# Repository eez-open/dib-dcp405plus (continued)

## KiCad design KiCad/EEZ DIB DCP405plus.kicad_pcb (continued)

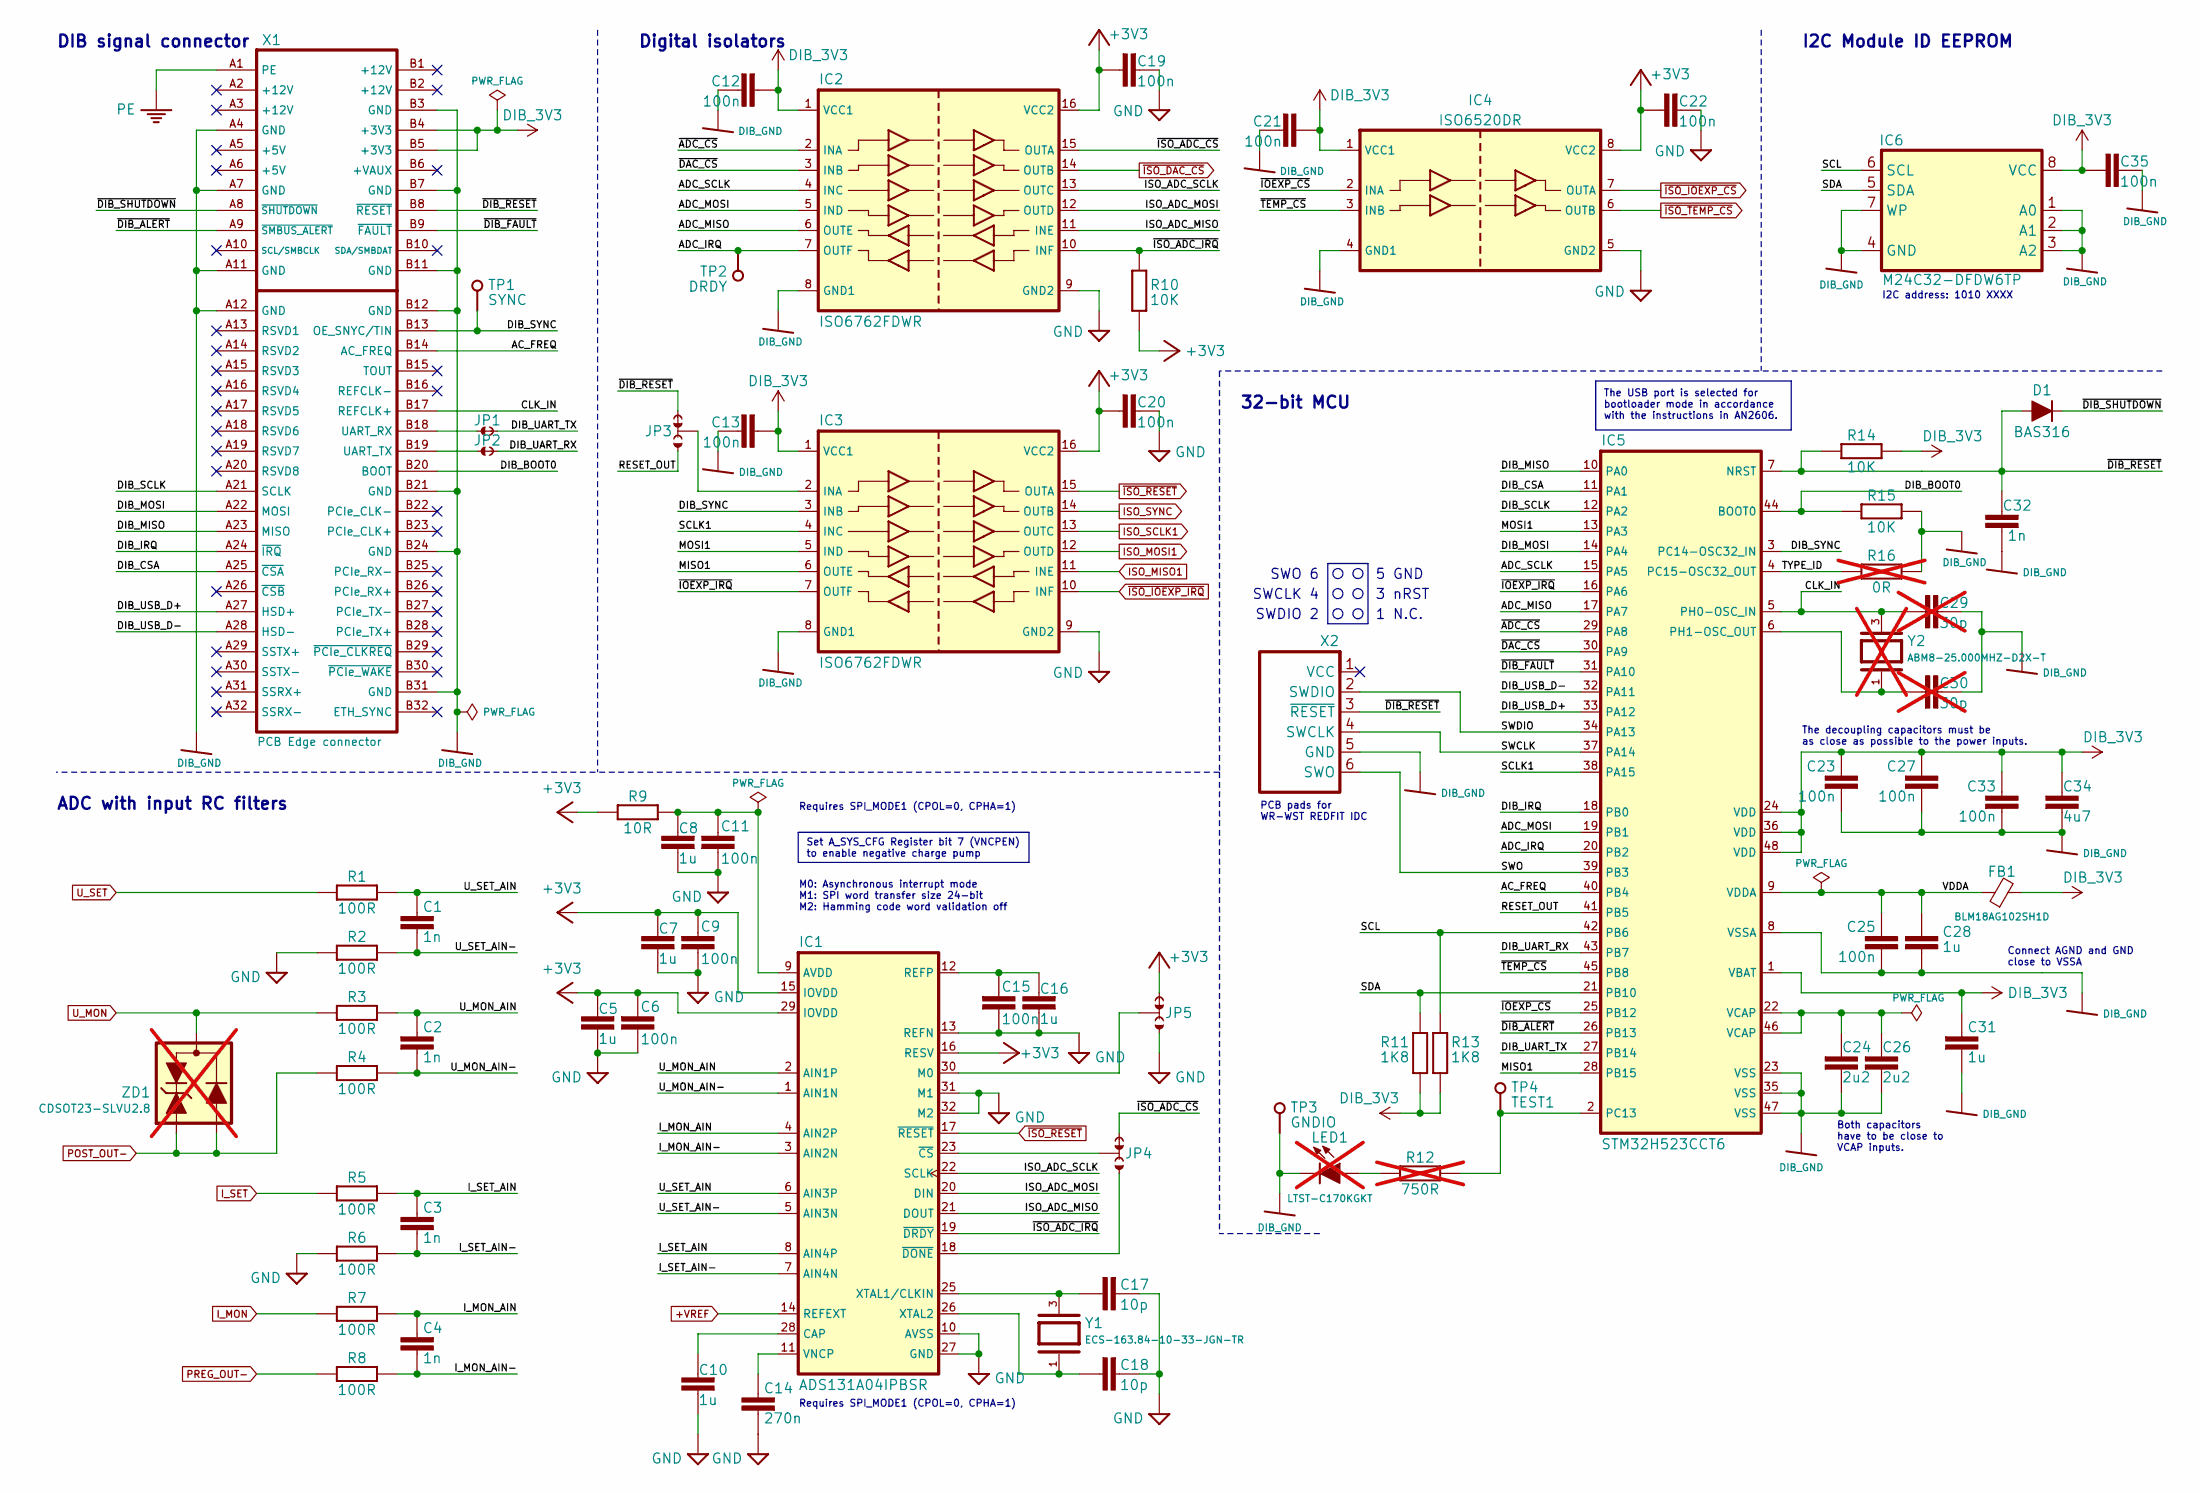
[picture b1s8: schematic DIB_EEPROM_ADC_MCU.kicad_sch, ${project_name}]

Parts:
C1, C2, C3, C4, C32: 1n; C_0603_1608Metric; DigiKey 1276-1018-1-ND
C5, C7, C8, C10, C16, C28, C31: 1u; C_0805_2012Metric; DigiKey 1276-2931-1-ND
C6, C9, C11, C12, C13, C15, C19, C20, C21, C22, C23, C25, C27, C33, C35: 100n; C_0603_1608Metric; DigiKey 1276-6717-1-ND
C14: 270n; C_0603_1608Metric; DigiKey 490-16405-1-ND
C17, C18: 10p; C_0603_1608Metric; DigiKey 1276-2149-1-ND
C24, C26: 2u2; C_0603_1608Metric; DigiKey 490-12332-1-ND
C29, C30: 30p; C_0603_1608Metric; DigiKey 1292-1515-1-ND; not fitted
C34: 4u7; C_0805_2012Metric; DigiKey 1276-2415-1-ND
D1: BAS316; SOD-323_1P8X1P35_ONS-M; DigiKey 5399-BAS316CT-ND
FB1: BLM18AG102SH1D; BEAD0603; DigiKey 490-7809-1-ND
IC1: ADS131A04IPBSR; QFP50P700X700X120-32N; DigiKey 296-44202-1-ND
IC2, IC3: ISO6762FDWR; DW16; DigiKey 296-ISO6762FDWRCT-ND
IC4: ISO6520DR; SOIC127P600X173-8N; DigiKey 296-ISO6520DRCT-ND
IC5: STM32H523CCT6; LQFP-48_7X7MM; DigiKey 497-STM32H523CCT6-ND
IC6: M24C32-DFDW6TP; TSSOP-8; DigiKey 497-16067-1-ND
JP1, JP2: JP2 shorted (0603)
JP3, JP4, JP5: 0R; JP3 shorted (0603)
LED1: LTST-C170KGKT; LED_LTST-C170KGKT_LTO-L; DigiKey 160-1414-2-ND; not fitted
R1, R2, R3, R4, R5, R6, R7, R8: 100R; R_0603_1608Metric; DigiKey 13-RC0603FR-10100RLCT-ND
R9: 10R; R_0805_2012Metric; DigiKey 311-10.0CRCT-ND
R10, R14, R15: 10K; R_0805_2012Metric; DigiKey 311-10.0KCRCT-ND
R11, R13: 1K8; R_0805_2012Metric; DigiKey 311-1.80KCRCT-ND
R12: 750R; R_0805_2012Metric; DigiKey A126385CT-ND; not fitted
R16: 0R; R_0603_1608Metric; not fitted
TP1, TP2, TP3, TP4: TEST-PIN_0.9MM; Testhole 24_50mils
X1: PCB Edge connector; DIB 2.0 edge card connector
X2: N.C.; WR-WST_490107670612_DEBUG
Y1: ECS-163.84-10-33-JGN-TR; XTAL_403C11A24M00000; DigiKey 535-9676-1-ND
Y2: ABM8-25.000MHZ-D2X-T; XTAL_403C11A24M00000; DigiKey 535-14398-1-ND; not fitted
ZD1: CDSOT23-SLVU2.8; SOT23-3; DigiKey CDSOT23-SLVU2.8TR-ND; not fitted

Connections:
+3V3: C5.1, C6.2, C7.1, C9.2, C19.2, C20.2, C22.2, IC1.15 (IOVDD), IC1.16 (RESV), IC1.29 (IOVDD), IC2.16 (VCC2), IC3.16 (VCC2), IC4.8 (VCC2), JP5.NC, R9.1, R10.1; also elsewhere on the board
+VREF: IC1.14 (REFEXT); also elsewhere on the board
/DIB isolators, EEPROM, ADC, MCU/AC_FREQ: IC5.40 (PB4), X1.B14 (AC_FREQ)
/DIB isolators, EEPROM, ADC, MCU/ADC_IRQ: IC2.7 (OUTF), IC5.20 (PB2), TP2.1 (P$1_1)
/DIB isolators, EEPROM, ADC, MCU/ADC_MISO: IC2.6 (OUTE), IC5.17 (PA7)
/DIB isolators, EEPROM, ADC, MCU/ADC_MOSI: IC2.5 (IND), IC5.19 (PB1)
/DIB isolators, EEPROM, ADC, MCU/ADC_SCLK: IC2.4 (INC), IC5.15 (PA5)
/DIB isolators, EEPROM, ADC, MCU/CLK_IN: C29.2, IC5.5 (PH0-OSC_IN), X1.B17 (REFCLK+), Y2.3
/DIB isolators, EEPROM, ADC, MCU/DIB_BOOT0: IC5.44 (BOOT0), R15.2, X1.B20 (BOOT)
/DIB isolators, EEPROM, ADC, MCU/DIB_CSA: IC5.11 (PA1), X1.A25 (~CSA)
/DIB isolators, EEPROM, ADC, MCU/DIB_IRQ: IC5.18 (PB0), X1.A24 (~IRQ)
/DIB isolators, EEPROM, ADC, MCU/DIB_MISO: IC5.10 (PA0), X1.A23 (MISO)
/DIB isolators, EEPROM, ADC, MCU/DIB_MOSI: IC5.14 (PA4), X1.A22 (MOSI)
/DIB isolators, EEPROM, ADC, MCU/DIB_SCLK: IC5.12 (PA2), X1.A21 (SCLK)
/DIB isolators, EEPROM, ADC, MCU/DIB_SYNC: IC3.3 (INB), IC5.3 (PC14-OSC32_IN), TP1.1 (P$1_1), X1.B13 (OE_SNYC/TIN)
/DIB isolators, EEPROM, ADC, MCU/DIB_UART_RX: IC5.43 (PB7), JP2.2
/DIB isolators, EEPROM, ADC, MCU/DIB_UART_TX: IC5.27 (PB14), JP1.2
/DIB isolators, EEPROM, ADC, MCU/DIB_USB_D+: IC5.33 (PA12), X1.A27 (HSD+)
/DIB isolators, EEPROM, ADC, MCU/DIB_USB_D-: IC5.32 (PA11), X1.A28 (HSD-)
/DIB isolators, EEPROM, ADC, MCU/ISO_ADC_MISO: IC1.21 (DOUT), IC2.11 (INE)
/DIB isolators, EEPROM, ADC, MCU/ISO_ADC_MOSI: IC1.20 (DIN), IC2.12 (OUTD)
/DIB isolators, EEPROM, ADC, MCU/ISO_ADC_SCLK: IC1.22 (SCLK), IC2.13 (OUTC)
/DIB isolators, EEPROM, ADC, MCU/I_MON_AIN: C4.2, IC1.4 (AIN2P), R7.1
/DIB isolators, EEPROM, ADC, MCU/I_MON_AIN-: C4.1, IC1.3 (AIN2N), R8.1
/DIB isolators, EEPROM, ADC, MCU/I_SET_AIN: C3.2, IC1.8 (AIN4P), R5.1
/DIB isolators, EEPROM, ADC, MCU/I_SET_AIN-: C3.1, IC1.7 (AIN4N), R6.1
/DIB isolators, EEPROM, ADC, MCU/MISO1: IC3.6 (OUTE), IC5.28 (PB15)
/DIB isolators, EEPROM, ADC, MCU/MOSI1: IC3.5 (IND), IC5.13 (PA3)
/DIB isolators, EEPROM, ADC, MCU/RESET_OUT: IC5.41 (PB5), JP3.NO
/DIB isolators, EEPROM, ADC, MCU/SCL: IC5.42 (PB6), IC6.6 (SCL), R13.2
/DIB isolators, EEPROM, ADC, MCU/SCLK1: IC3.4 (INC), IC5.38 (PA15)
/DIB isolators, EEPROM, ADC, MCU/SDA: IC5.21 (PB10), IC6.5 (SDA), R11.2
/DIB isolators, EEPROM, ADC, MCU/SWCLK: IC5.37 (PA14), X2.4 (SWCLK)
/DIB isolators, EEPROM, ADC, MCU/SWDIO: IC5.34 (PA13), X2.2 (SWDIO)
/DIB isolators, EEPROM, ADC, MCU/SWO: IC5.39 (PB3), X2.6 (SWO)
/DIB isolators, EEPROM, ADC, MCU/TYPE_ID: IC5.4 (PC15-OSC32_OUT), R16.2
/DIB isolators, EEPROM, ADC, MCU/U_MON_AIN: C2.1, IC1.2 (AIN1P), R3.1
/DIB isolators, EEPROM, ADC, MCU/U_MON_AIN-: C2.2, IC1.1 (AIN1N), R4.1
/DIB isolators, EEPROM, ADC, MCU/U_SET_AIN: C1.2, IC1.6 (AIN3P), R1.1
/DIB isolators, EEPROM, ADC, MCU/U_SET_AIN-: C1.1, IC1.5 (AIN3N), R2.1
/DIB isolators, EEPROM, ADC, MCU/VDDA: C25.1, C28.2, FB1.1, IC5.9 (VDDA)
/DIB isolators, EEPROM, ADC, MCU/~ADC_CS: IC2.2 (INA), IC5.29 (PA8)
/DIB isolators, EEPROM, ADC, MCU/~DAC_CS: IC2.3 (INB), IC5.30 (PA9)
/DIB isolators, EEPROM, ADC, MCU/~DIB_ALERT: IC5.26 (PB13), X1.A9 (~SMBUS_ALERT)
/DIB isolators, EEPROM, ADC, MCU/~DIB_FAULT: IC5.31 (PA10), X1.B9 (~FAULT)
/DIB isolators, EEPROM, ADC, MCU/~DIB_RESET: C32.2, D1.A, IC5.7 (NRST), JP3.NC, R14.1, X1.B8 (~RESET), X2.3 (~RESET)
/DIB isolators, EEPROM, ADC, MCU/~DIB_SHUTDOWN: D1.C, X1.A8 (~SHUTDOWN)
/DIB isolators, EEPROM, ADC, MCU/~IOEXP_CS: IC4.2 (INA), IC5.25 (PB12)
/DIB isolators, EEPROM, ADC, MCU/~IOEXP_IRQ: IC3.7 (OUTF), IC5.16 (PA6)
/DIB isolators, EEPROM, ADC, MCU/~ISO_ADC_CS: IC2.15 (OUTA), JP4.NC
/DIB isolators, EEPROM, ADC, MCU/~ISO_ADC_IRQ: IC1.19 (~DRDY), IC2.10 (INF), R10.2
/DIB isolators, EEPROM, ADC, MCU/~TEMP_CS: IC4.3 (INB), IC5.45 (PB8)
DIB_3V3: C12.2, C13.2, C21.2, C23.1, C27.1, C31.2, C33.1, C34.1, C35.2, FB1.2, IC2.1 (VCC1), IC3.1 (VCC1), IC4.1 (VCC1), IC5.1 (VBAT), IC5.24 (VDD), IC5.36 (VDD), IC5.48 (VDD), IC6.8 (VCC), R11.1, R13.1, R14.2, X1.B4 (+3V3), X1.B5 (+3V3)
DIB_GND: C12.1, C13.1, C21.1, C23.2, C24.1, C25.2, C26.1, C27.2, C28.1, C29.1, C30.1, C31.1, C32.1, C33.2, C34.2, C35.1, IC2.8 (GND1), IC3.8 (GND1), IC4.4 (GND1), IC5.8 (VSSA), IC5.23 (VSS), IC5.35 (VSS), IC5.47 (VSS), IC6.1 (A0), IC6.2 (A1), IC6.3 (A2), IC6.4 (GND), IC6.7 (WP), LED1.C, R15.1, R16.1, TP3.1 (P$1_1), X1.A4 (GND), X1.A7 (GND), X1.A11 (GND), X1.A12 (GND), X1.B3 (GND), X1.B7 (GND), X1.B11 (GND), X1.B12 (GND), X1.B21 (GND), X1.B24 (GND), X1.B31 (GND), X2.5 (GND)
GND: C5.2, C6.1, C7.2, C8.2, C9.1, C10.2, C11.1, C14.1, C15.1, C16.2, C17.1, C18.1, C19.1, C20.1, C22.1, IC1.10 (AVSS), IC1.13 (REFN), IC1.27 (GND), IC1.31 (M1), IC1.32 (M2), IC2.9 (GND2), IC3.9 (GND2), IC4.5 (GND2), JP5.NO, R2.2, R6.2; also elsewhere on the board
ISO_MISO1: IC3.11 (INE); also elsewhere on the board
ISO_MOSI1: IC3.12 (OUTD); also elsewhere on the board
ISO_SCLK1: IC3.13 (OUTC); also elsewhere on the board
ISO_SYNC: IC3.14 (OUTB); also elsewhere on the board
I_MON: R7.2; also elsewhere on the board
I_SET: R5.2; also elsewhere on the board
unnamed: C24.2, C26.2, IC5.22 (VCAP), IC5.46 (VCAP)
unnamed: C8.1, C11.2, IC1.9 (AVDD), R9.2
unnamed: C10.1, IC1.28 (CAP)
unnamed: IC1.30 (M0), JP5.COM
unnamed: C15.2, C16.1, IC1.12 (REFP)
unnamed: C14.2, IC1.11 (VNCP)
unnamed: C17.2, IC1.25 (XTAL1/CLKIN), Y1.3
unnamed: C18.2, IC1.26 (XTAL2), Y1.1
unnamed: IC1.23 (~CS), JP4.COM
unnamed: IC1.18 (~DONE), JP4.NO
unnamed: IC3.2 (INA), JP3.COM
unnamed: IC5.2 (PC13), R12.2, TP4.1 (P$1_1)
unnamed: C30.2, IC5.6 (PH1-OSC_OUT), Y2.1
unnamed: LED1.A, R12.1
unnamed: JP1.1, X1.B18 (UART_RX)
unnamed: JP2.1, X1.B19 (UART_TX)
PE: X1.A1 (PE); also elsewhere on the board
POST_OUT-: R4.2, ZD1.1, ZD1.2; also elsewhere on the board
PREG_OUT-: R8.2; also elsewhere on the board
U_MON: R3.2, ZD1.3; also elsewhere on the board
U_SET: R1.2; also elsewhere on the board
~ISO_DAC_CS: IC2.14 (OUTB); also elsewhere on the board
~ISO_IOEXP_CS: IC4.7 (OUTA); also elsewhere on the board
~ISO_IOEXP_IRQ: IC3.10 (INF); also elsewhere on the board
~ISO_RESET: IC1.17 (~RESET), IC3.15 (OUTA); also elsewhere on the board
~ISO_TEMP_CS: IC4.6 (OUTB); also elsewhere on the board

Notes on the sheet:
Digital isolators
Requires SPI_MODE1 (CPOL=0, CPHA=1)
DIB signal connector
3 nRST
SWCLK 4
32-bit MCU
The decoupling capacitors must be as close as possible to the power inputs.
1 N.C.
SWO 6
ADC with input RC filters
I2C address: 1010 XXXX
PCB pads for WR-WST REDFIT IDC
SWDIO 2
5 GND
Connect AGND and GND close to VSSA
M0: Asynchronous interrupt mode M1: SPI word transfer size 24-bit M2: Hamming code word validation off
I2C Module ID EEPROM
Both capacitors have to be close to VCAP inputs.
Set A_SYS_CFG Register bit 7 (VNCPEN) to enable negative charge pump
The USB port is selected for bootloader mode in accordance with the instructions in AN2606.

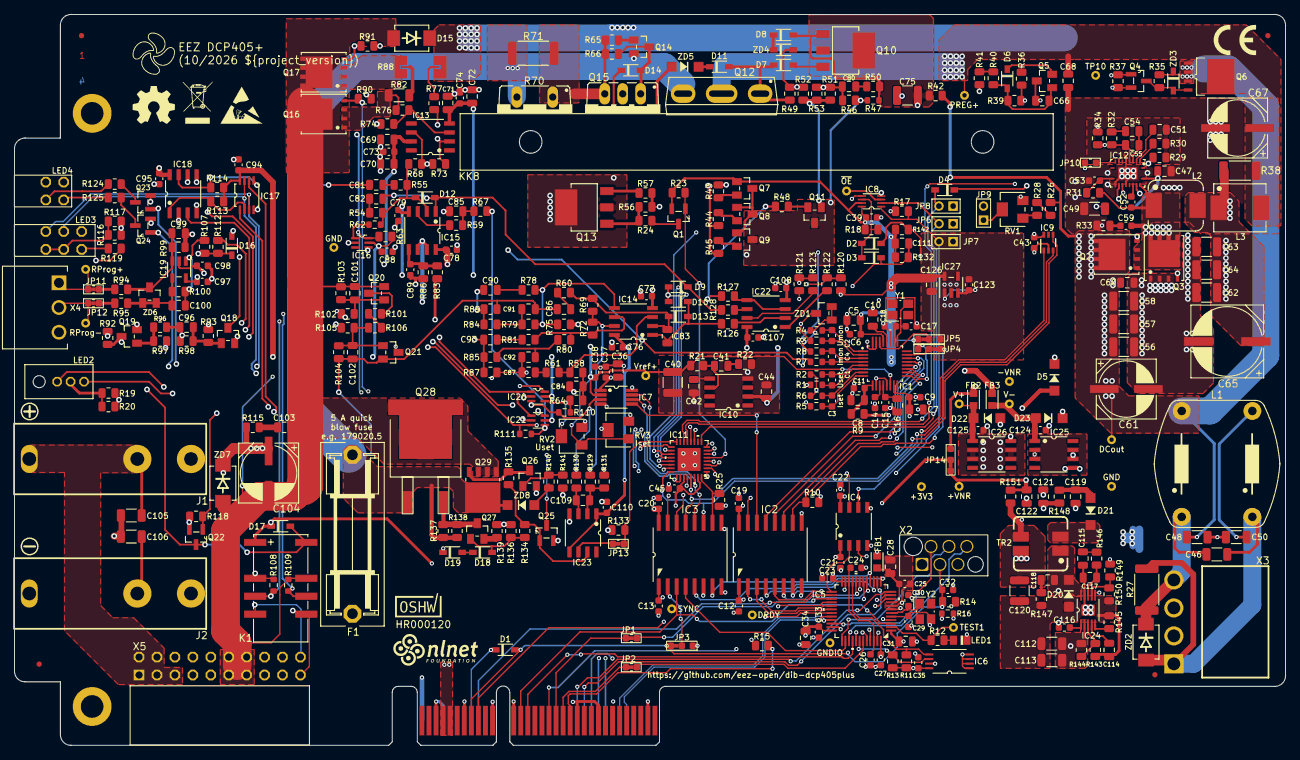
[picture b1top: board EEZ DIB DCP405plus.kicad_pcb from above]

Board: 4 copper layers, 180.0 x 103.5 mm, 437 parts (1 on the bottom side), 262 nets.

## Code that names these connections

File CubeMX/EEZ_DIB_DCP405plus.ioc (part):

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Mcu.Name=STM32H503CBTx
Mcu.Package=LQFP48
Mcu.UserName=STM32H503CBTx
PA0.GPIOParameters=GPIO_Speed,GPIO_Label
PA0.GPIO_Label=DIB_MISO
PA0.GPIO_Speed=GPIO_SPEED_FREQ_LOW
PA0.Mode=Full_Duplex_Slave
PA0.Signal=SPI1_MISO
PA1.GPIOParameters=GPIO_Speed,GPIO_Label
PA1.GPIO_Label=DIB_CSA
PA1.GPIO_Speed=GPIO_SPEED_FREQ_LOW
PA1.Mode=NSS_Signal_Hard_Input
PA1.Signal=SPI1_NSS
PA10.GPIOParameters=GPIO_Label
PA10.GPIO_Label=DIB_FAULT
PA10.Signal=GPIO_Output
PA11.Mode=Device
PA11.Signal=USB_DM
PA12.Mode=Device
PA12.Signal=USB_DP
PA13(JTMS/SWDIO).GPIOParameters=GPIO_Label
PA13(JTMS/SWDIO).GPIO_Label=JTAG_DIO
PA13(JTMS/SWDIO).Mode=Trace_Asynchronous_SW
PA13(JTMS/SWDIO).Signal=DEBUG_JTMS-SWDIO
PA14(JTCK/SWCLK).GPIOParameters=GPIO_Label
PA14(JTCK/SWCLK).GPIO_Label=JTAG_CLK
PA14(JTCK/SWCLK).Mode=Trace_Asynchronous_SW
PA14(JTCK/SWCLK).Signal=DEBUG_JTCK-SWCLK
PA15(JTDI).GPIOParameters=GPIO_Speed,GPIO_Label
PA15(JTDI).GPIO_Label=SCLK1
PA15(JTDI).GPIO_Speed=GPIO_SPEED_FREQ_HIGH
PA15(JTDI).Mode=Full_Duplex_Master
PA15(JTDI).Signal=SPI3_SCK
PA2.GPIOParameters=GPIO_Speed,GPIO_Label
PA2.GPIO_Label=DIB_CLK
PA2.GPIO_Speed=GPIO_SPEED_FREQ_LOW
PA2.Mode=Full_Duplex_Slave
PA2.Signal=SPI1_SCK
PA3.GPIOParameters=GPIO_Speed,GPIO_Label
PA3.GPIO_Label=MOSI1
PA3.GPIO_Speed=GPIO_SPEED_FREQ_HIGH
PA3.Mode=Full_Duplex_Master
PA3.Signal=SPI3_MOSI
PA4.GPIOParameters=GPIO_Speed,GPIO_Label
PA4.GPIO_Label=DIB_MOSI
PA4.GPIO_Speed=GPIO_SPEED_FREQ_LOW
PA4.Mode=Full_Duplex_Slave
PA4.Signal=SPI1_MOSI
PA5.GPIOParameters=GPIO_Speed,GPIO_Label
PA5.GPIO_Label=ADC_SCLK
PA5.GPIO_Speed=GPIO_SPEED_FREQ_VERY_HIGH
PA5.Mode=Full_Duplex_Master
PA5.Signal=SPI2_SCK
PA6.GPIOParameters=GPIO_Label
PA6.GPIO_Label=IOEXP_IRQ
PA6.Signal=GPXTI6
PA7.GPIOParameters=GPIO_Speed,GPIO_Label
PA7.GPIO_Label=ADC_MISO
PA7.GPIO_Speed=GPIO_SPEED_FREQ_VERY_HIGH
PA7.Mode=Full_Duplex_Master
PA7.Signal=SPI2_MISO
PA8.GPIOParameters=PinState,GPIO_Label
PA8.GPIO_Label=ADC_CS
PA8.PinState=GPIO_PIN_SET
PA8.Signal=GPIO_Output
PA9.GPIOParameters=PinState,GPIO_Label
PA9.GPIO_Label=DAC_CS
PA9.PinState=GPIO_PIN_SET
PA9.Signal=GPIO_Output
PB0.GPIOParameters=PinState,GPIO_Label
PB0.GPIO_Label=DIB_IRQ
PB0.PinState=GPIO_PIN_SET
PB0.Signal=GPIO_Output
PB1.GPIOParameters=GPIO_Speed,GPIO_Label
PB1.GPIO_Label=ADC_MOSI
PB1.GPIO_Speed=GPIO_SPEED_FREQ_VERY_HIGH
PB1.Mode=Full_Duplex_Master
PB1.Signal=SPI2_MOSI
PB10.GPIOParameters=GPIO_Label
PB10.GPIO_Label=DIB_SDA
PB10.Mode=SMBus-Alert-mode
PB10.Signal=I2C1_SDA
PB12.GPIOParameters=PinState,GPIO_Label
PB12.GPIO_Label=IOEXP_CS
PB12.PinState=GPIO_PIN_SET
PB12.Signal=GPIO_Output
PB13.GPIOParameters=GPIO_Label
PB13.GPIO_Label=DIB_ALERT
PB13.Mode=SMBus-Alert-mode
PB13.Signal=I2C1_SMBA
PB14.Mode=Asynchronous
PB14.Signal=USART1_TX
PB15.GPIOParameters=GPIO_Speed,GPIO_Label
PB15.GPIO_Label=MISO1
PB15.GPIO_Speed=GPIO_SPEED_FREQ_HIGH
PB15.Mode=Full_Duplex_Master
PB15.Signal=SPI3_MISO
PB2.GPIOParameters=GPIO_Label
PB2.GPIO_Label=ADC_IRQ
PB2.Signal=GPIO_Input
PB3(JTDO/TRACESWO).GPIOParameters=GPIO_Label
PB3(JTDO/TRACESWO).GPIO_Label=JTAG_SWO
PB3(JTDO/TRACESWO).Mode=Trace_Asynchronous_SW
PB3(JTDO/TRACESWO).Signal=DEBUG_JTDO-SWO
PB4(NJTRST).GPIOParameters=GPIO_Label
PB4(NJTRST).GPIO_Label=AC_FREQ
PB4(NJTRST).Signal=S_TIM1_CH2
PB6.GPIOParameters=GPIO_Label
PB6.GPIO_Label=DIB_SCL
PB6.Mode=SMBus-Alert-mode
PB6.Signal=I2C1_SCL
PB7.Mode=Asynchronous
PB7.Signal=USART1_RX
PB8.GPIOParameters=PinState,GPIO_Label
PB8.GPIO_Label=TEMP_CS
PB8.PinState=GPIO_PIN_SET
PB8.Signal=GPIO_Output
PC13.GPIOParameters=GPIO_Label
PC13.GPIO_Label=ACT_LED
PC13.Signal=GPIO_Output
PC15-OSC32_OUT(OSC32_OUT).GPIOParameters=GPIO_Label
PC15-OSC32_OUT(OSC32_OUT).GPIO_Label=TYPE_ID
PC15-OSC32_OUT(OSC32_OUT).Signal=GPIO_Input
PH0-OSC_IN(PH0).Mode=HSE-External-Oscillator
PH0-OSC_IN(PH0).Signal=RCC_OSC_IN
PH1-OSC_OUT(PH1).Mode=HSE-External-Oscillator
PH1-OSC_OUT(PH1).Signal=RCC_OSC_OUT
RCC.HSE_VALUE=25000000
RCC.SYSCLKFreq_VALUE=250000000
RCC.SYSCLKSource=RCC_SYSCLKSOURCE_PLLCLK
board=custom

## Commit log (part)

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2025-09-11 License added
2025-10-22 First KiCad project commit
2025-10-23 Schematics info updated
2025-10-23 JP symbols update
2025-10-23 Gerbers update
2025-10-23 Front mask DXF files
2026-01-03 X3 type changed
2026-01-06 DIB connector update
2026-01-07 OSHW certification mark, front mask STEP color
2026-02-17 Q18, Q19 model fixed
2026-02-17 BOM update
2026-02-25 JP3 update (Reset out select)
2026-03-01 #2, #3, image of the assembled module
2026-03-05 Pullups for OE indicator added
2026-03-05 Front mask silkscreen corrections
2026-03-13 Front mask gerbers update
2026-03-28 Silkscreen updated
2026-04-29 OSHWA logo added, KiCad 10 migration
2026-05-10 Basic variant schematics PDF
2026-05-10 BOM and Gerbers update
2026-06-26 #8, schematics annotated
2026-06-30 Schematics update (power socket pinout)
